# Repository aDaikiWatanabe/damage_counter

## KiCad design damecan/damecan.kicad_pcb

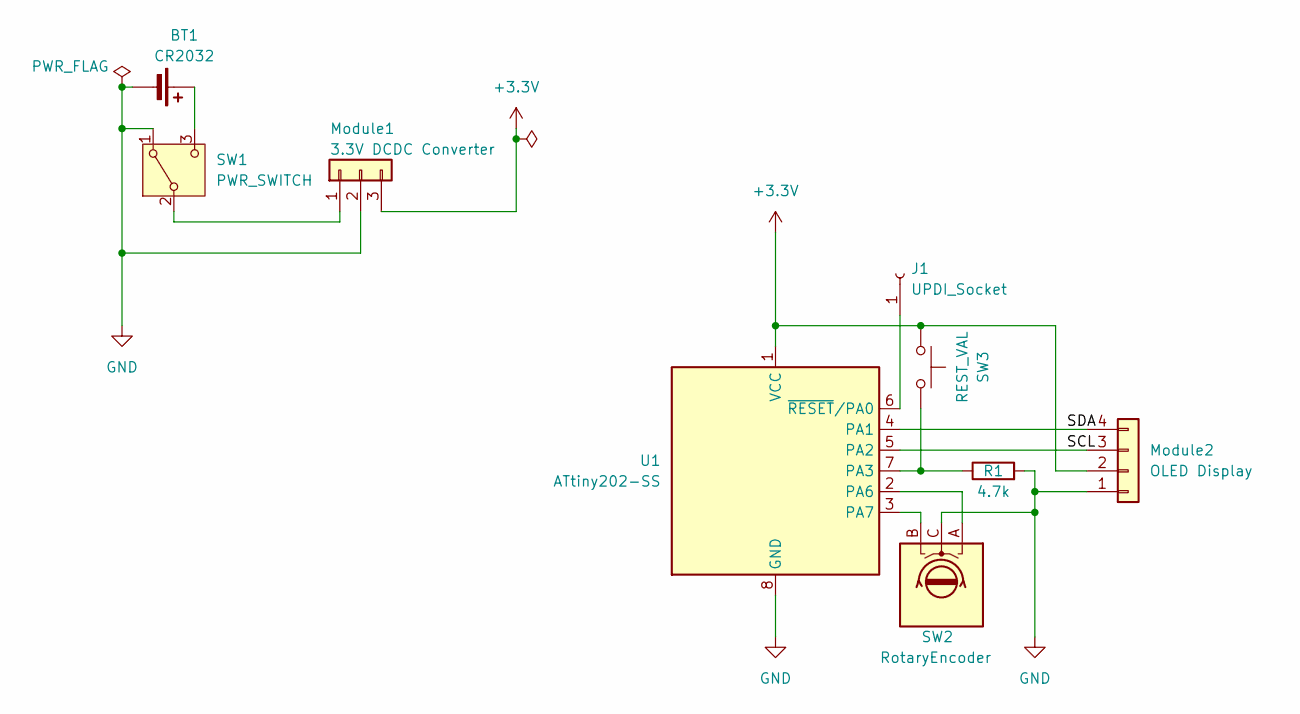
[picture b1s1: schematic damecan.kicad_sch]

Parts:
BT1: CR2032; CH075-2032LF
J1: UPDI_Socket; PinSocket_1x01_P1.27mm_Vertical
Module1: 3.3V DCDC Converter; 3.3V 出力昇圧DCDCコンバータ
Module2: OLED Display; OLEDディスプレイ 128x64
R1: 4.7k; R_Axial_DIN0204_L3.6mm_D1.6mm_P5.08mm_Horizontal
SW1: PWR_SWITCH; スライドスイッチ 1回路2接点
SW2: RotaryEncoder; RotaryEncoder_Alps_EC12E_Vertical_H20mm
SW3: REST_VAL; SW_PUSH_6mm
U1: ATtiny202-SS; SOIC-8_3.9x4.9mm_P1.27mm

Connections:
+3.3V: Module1.3, Module2.2, SW3.1, U1.1 (VCC)
/SCL: Module2.3, U1.5 (PA2)
/SDA: Module2.4, U1.4 (PA1)
GND: BT1.2 (-), Module1.2, Module2.1, R1.2, SW1.1 (A), SW2.C, U1.8 (GND)
unnamed: BT1.1 (+), SW1.3 (C)
unnamed: J1.1, U1.6 (~RESET/PA0)
unnamed: Module1.1, SW1.2 (B)
unnamed: R1.1, SW3.2, U1.7 (PA3)
unnamed: SW2.A, U1.2 (PA6)
unnamed: SW2.B, U1.3 (PA7)

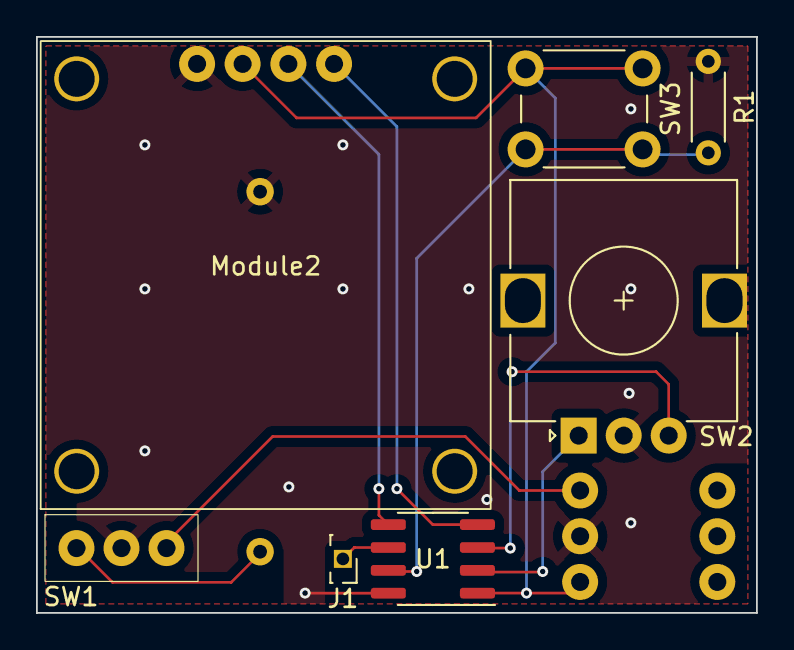
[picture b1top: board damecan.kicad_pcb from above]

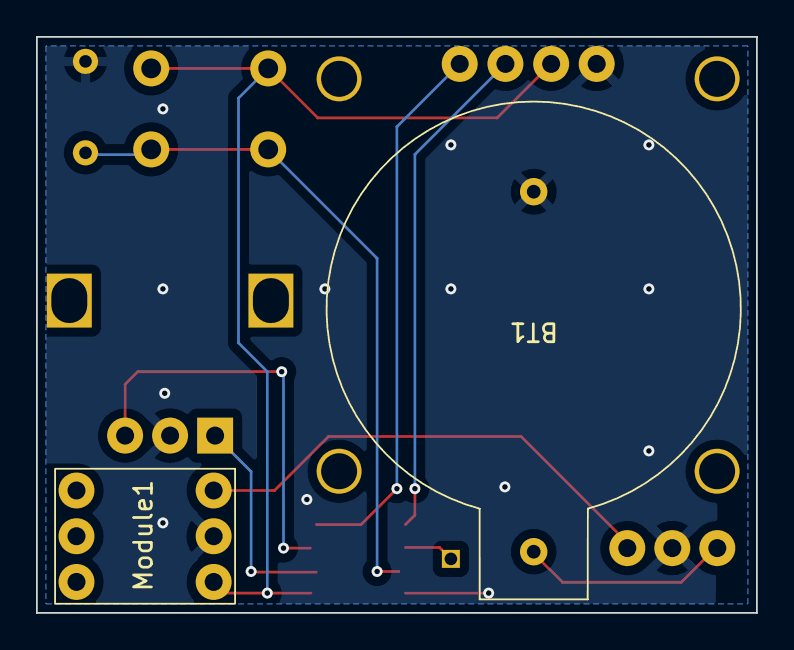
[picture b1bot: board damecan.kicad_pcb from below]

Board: 2 copper layers, 40.0 x 32.0 mm, 9 parts (2 on the bottom side), 10 nets.

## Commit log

2024-03-14 現状をcommit
2024-03-14 add gitignore
2024-03-29 レビュー後の改善
